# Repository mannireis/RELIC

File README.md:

# RELIC
A cool 40% ish keyboard that uses the XIAO BLE and has 36 keys.  

**KIcanvas Project Link:** [Open in KIcanvas](https://kicanvas.org/?github=https%3A%2F%2Fgithub.com%2Fmannireis%2FRELIC%2Fblob%2Fmain%2FPCB%2FRELIC.kicad_pro)

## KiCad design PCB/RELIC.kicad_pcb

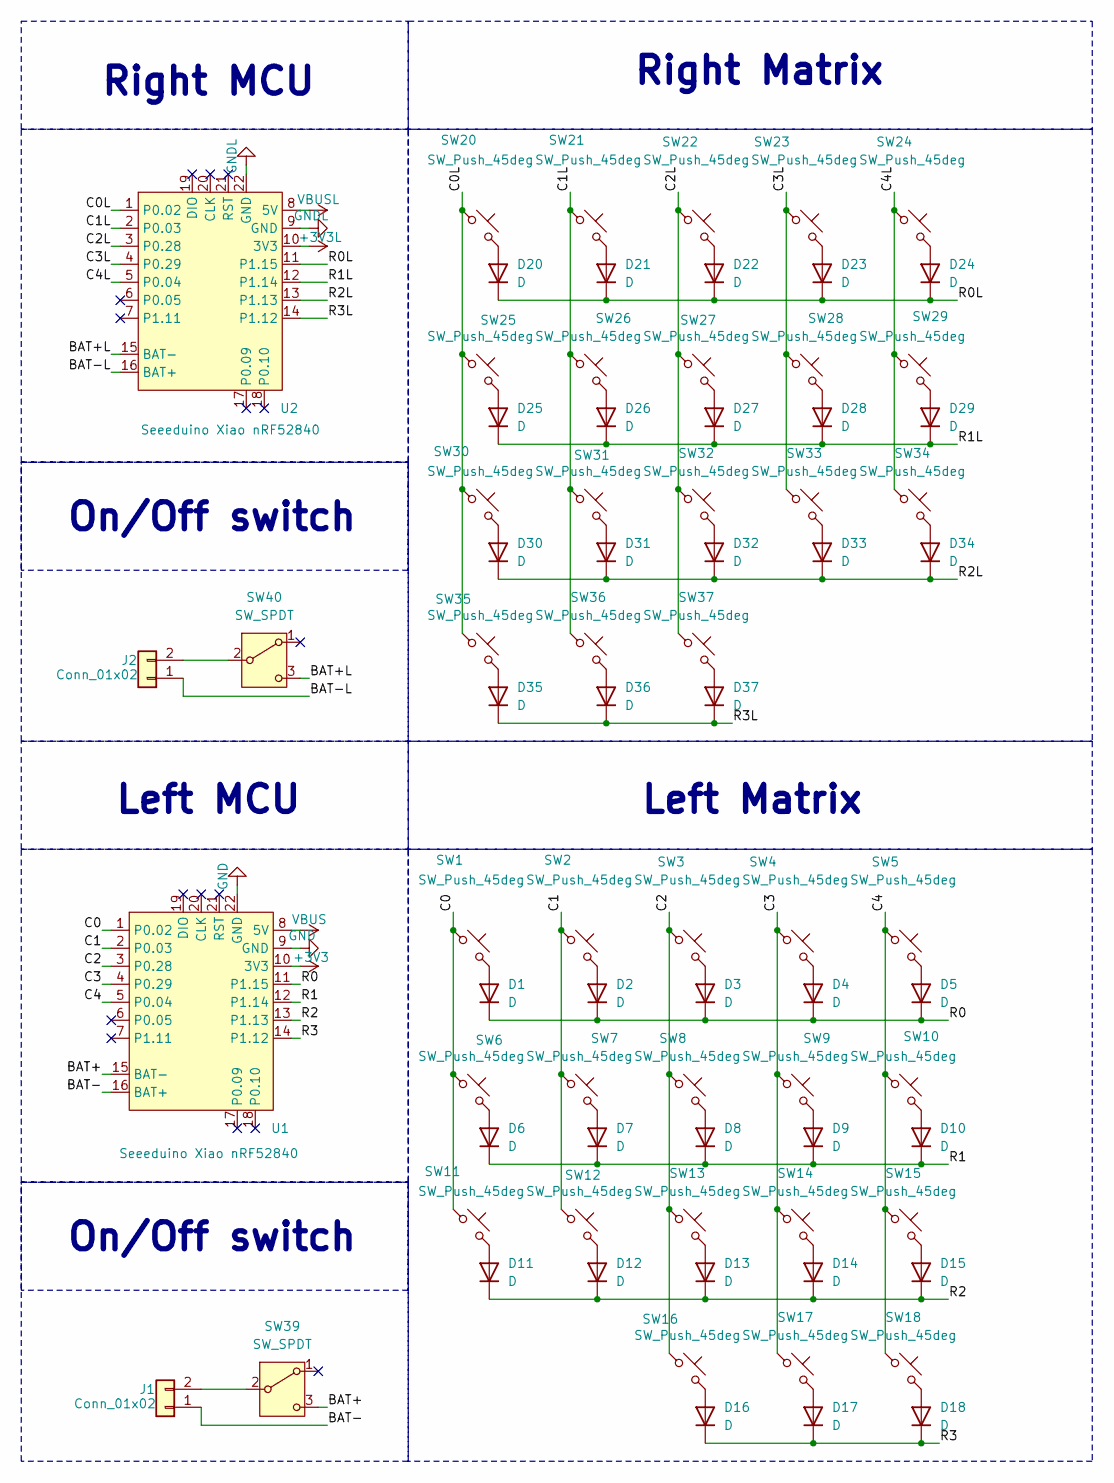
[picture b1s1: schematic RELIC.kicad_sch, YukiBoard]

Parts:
D1, D2, D3, D4, D5, D6, D7, D8, D9, D10, D11, D12, D13, D14, D15, D16, D17, D18, D20, D21, D22, D23, D24, D25, D26, D27, D28, D29, D30, D31, D32, D33, D34, D35, D36, D37: D; Diode_DO-35
J1, J2: Conn_01x02; PinHeader_1x02_P2.54mm_Vertical
SW1, SW2, SW3, SW4, SW5, SW6, SW7, SW8, SW9, SW10, SW11, SW12, SW13, SW14, SW15, SW16, SW17, SW18, SW20, SW21, SW22, SW23, SW24, SW25, SW26, SW27, SW28, SW29, SW30, SW31, SW32, SW33, SW34, SW35, SW36, SW37: SW_Push_45deg; MX-Hotswap-1U
SW39, SW40: SW_SPDT; Switch_MSK12C02
U1, U2: Seeeduino Xiao nRF52840; Xiao_nRF52840_ACH

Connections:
+3V3: U1.10 (3V3)
+3V3L: U2.10 (3V3)
/BAT+: SW39.3 (C), U1.15 (BAT-)
/BAT+L: SW40.3 (C), U2.15 (BAT-)
/BAT-: J1.1, U1.16 (BAT+)
/BAT-L: J2.1, U2.16 (BAT+)
/C0: SW1.1, SW6.1, SW11.1, U1.1 (P0.02)
/C0L: SW20.1, SW25.1, SW30.1, SW35.1, U2.1 (P0.02)
/C1: SW2.1, SW7.1, SW12.1, U1.2 (P0.03)
/C1L: SW21.1, SW26.1, SW31.1, SW36.1, U2.2 (P0.03)
/C2: SW3.1, SW8.1, SW13.1, SW16.1, U1.3 (P0.28)
/C2L: SW22.1, SW27.1, SW32.1, SW37.1, U2.3 (P0.28)
/C3: SW4.1, SW9.1, SW14.1, SW17.1, U1.4 (P0.29)
/C3L: SW23.1, SW28.1, SW33.1, U2.4 (P0.29)
/C4: SW5.1, SW10.1, SW15.1, SW18.1, U1.5 (P0.04)
/C4L: SW24.1, SW29.1, SW34.1, U2.5 (P0.04)
/R0: D1.1 (K), D2.1 (K), D3.1 (K), D4.1 (K), D5.1 (K), U1.11 (P1.15)
/R0L: D20.1 (K), D21.1 (K), D22.1 (K), D23.1 (K), D24.1 (K), U2.11 (P1.15)
/R1: D6.1 (K), D7.1 (K), D8.1 (K), D9.1 (K), D10.1 (K), U1.12 (P1.14)
/R1L: D25.1 (K), D26.1 (K), D27.1 (K), D28.1 (K), D29.1 (K), U2.12 (P1.14)
/R2: D11.1 (K), D12.1 (K), D13.1 (K), D14.1 (K), D15.1 (K), U1.13 (P1.13)
/R2L: D30.1 (K), D31.1 (K), D32.1 (K), D33.1 (K), D34.1 (K), U2.13 (P1.13)
/R3: D16.1 (K), D17.1 (K), D18.1 (K), U1.14 (P1.12)
/R3L: D35.1 (K), D36.1 (K), D37.1 (K), U2.14 (P1.12)
GND: U1.9 (GND), U1.22 (GND)
GNDL: U2.9 (GND), U2.22 (GND)
unnamed: D1.2 (A), SW1.2
unnamed: D2.2 (A), SW2.2
unnamed: D3.2 (A), SW3.2
unnamed: D4.2 (A), SW4.2
unnamed: D5.2 (A), SW5.2
unnamed: D6.2 (A), SW6.2
unnamed: D7.2 (A), SW7.2
unnamed: D8.2 (A), SW8.2
unnamed: D9.2 (A), SW9.2
unnamed: D10.2 (A), SW10.2
unnamed: D11.2 (A), SW11.2
unnamed: D12.2 (A), SW12.2
unnamed: D13.2 (A), SW13.2
unnamed: D14.2 (A), SW14.2
unnamed: D15.2 (A), SW15.2
unnamed: D16.2 (A), SW16.2
unnamed: D17.2 (A), SW17.2
unnamed: D18.2 (A), SW18.2
unnamed: D20.2 (A), SW20.2
unnamed: D21.2 (A), SW21.2
unnamed: D22.2 (A), SW22.2
unnamed: D23.2 (A), SW23.2
unnamed: D24.2 (A), SW24.2
unnamed: D25.2 (A), SW25.2
unnamed: D26.2 (A), SW26.2
unnamed: D27.2 (A), SW27.2
unnamed: D28.2 (A), SW28.2
unnamed: D29.2 (A), SW29.2
unnamed: D30.2 (A), SW30.2
unnamed: D31.2 (A), SW31.2
unnamed: D32.2 (A), SW32.2
unnamed: D33.2 (A), SW33.2
unnamed: D34.2 (A), SW34.2
unnamed: D35.2 (A), SW35.2
unnamed: D36.2 (A), SW36.2
unnamed: D37.2 (A), SW37.2
unnamed: J1.2, SW39.2 (B)
unnamed: J2.2, SW40.2 (B)
VBUS: U1.8 (5V)
VBUSL: U2.8 (5V)

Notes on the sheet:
Right Matrix
Left Matrix
Left MCU
On/Off switch
Right MCU

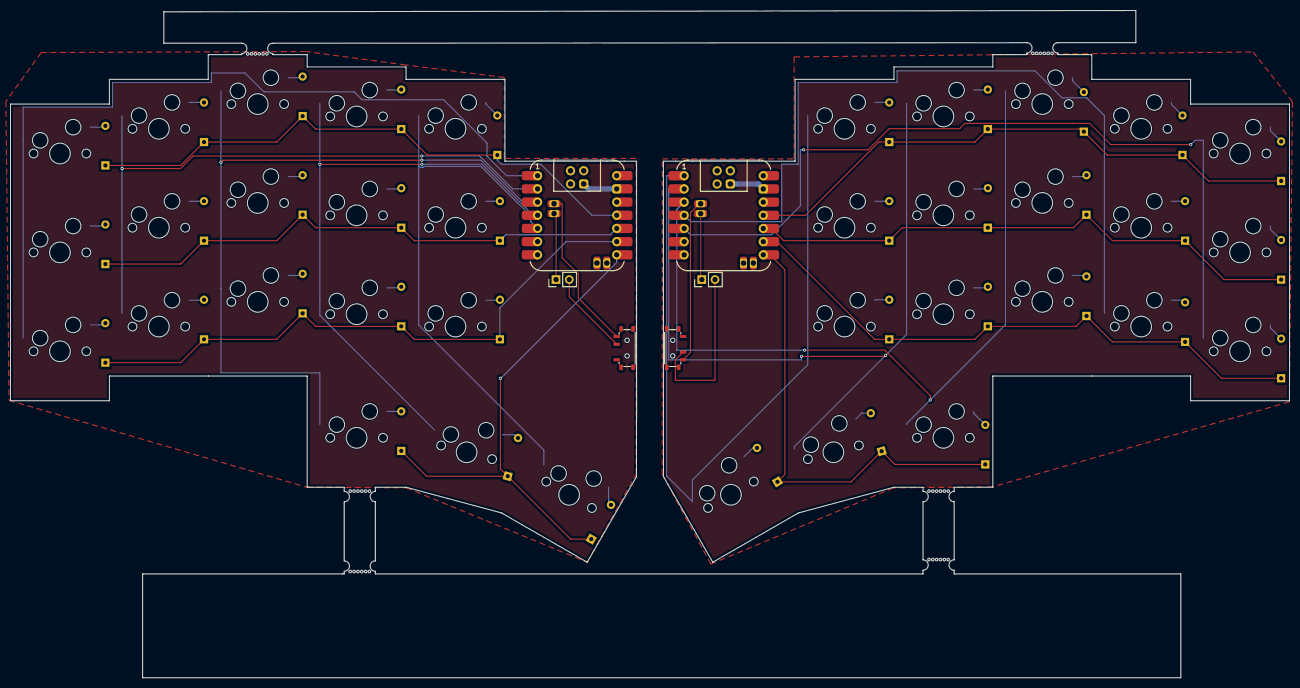
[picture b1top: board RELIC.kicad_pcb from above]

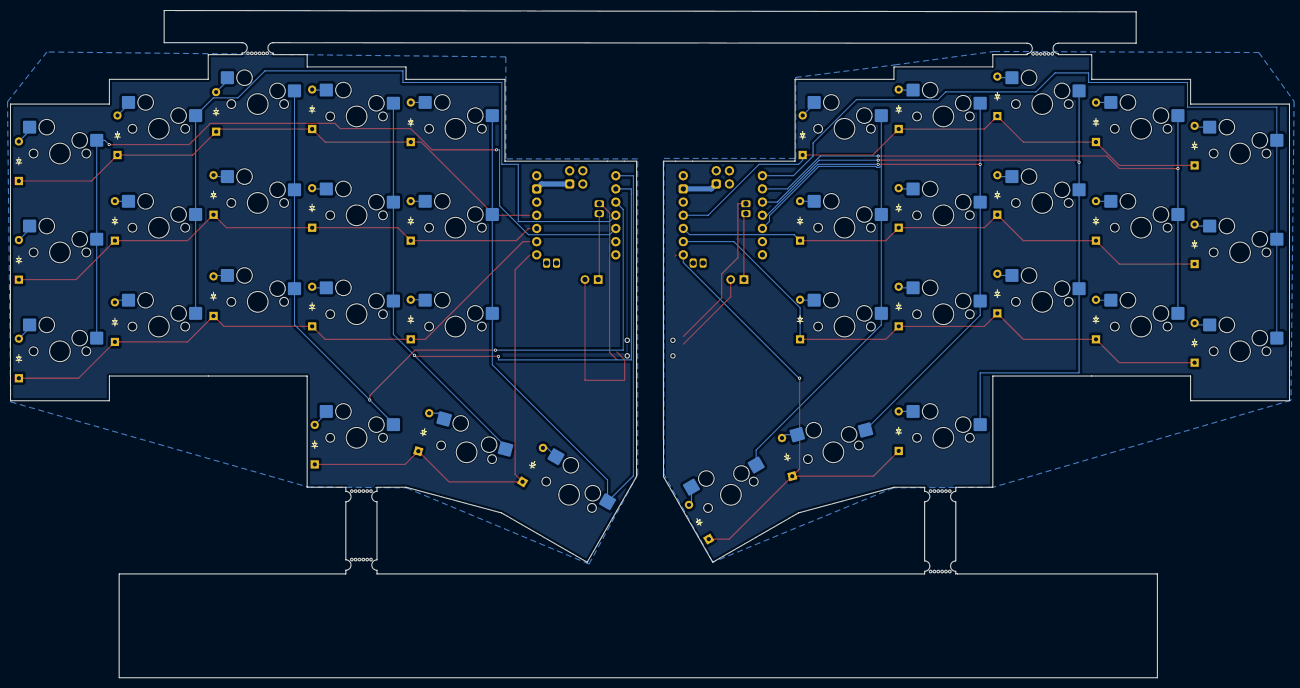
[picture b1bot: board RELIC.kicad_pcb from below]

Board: 2 copper layers, 246.4 x 128.5 mm, 78 parts (72 on the bottom side), 62 nets.

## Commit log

2025-08-01 not working the commint?
2025-08-01 Add cool stuff to pcb 󰇳
2025-08-01 Add the step file
2025-08-08 Add stuf
2025-08-11 Rename stuff
2025-08-14 readme stuff
2025-11-09 meow
